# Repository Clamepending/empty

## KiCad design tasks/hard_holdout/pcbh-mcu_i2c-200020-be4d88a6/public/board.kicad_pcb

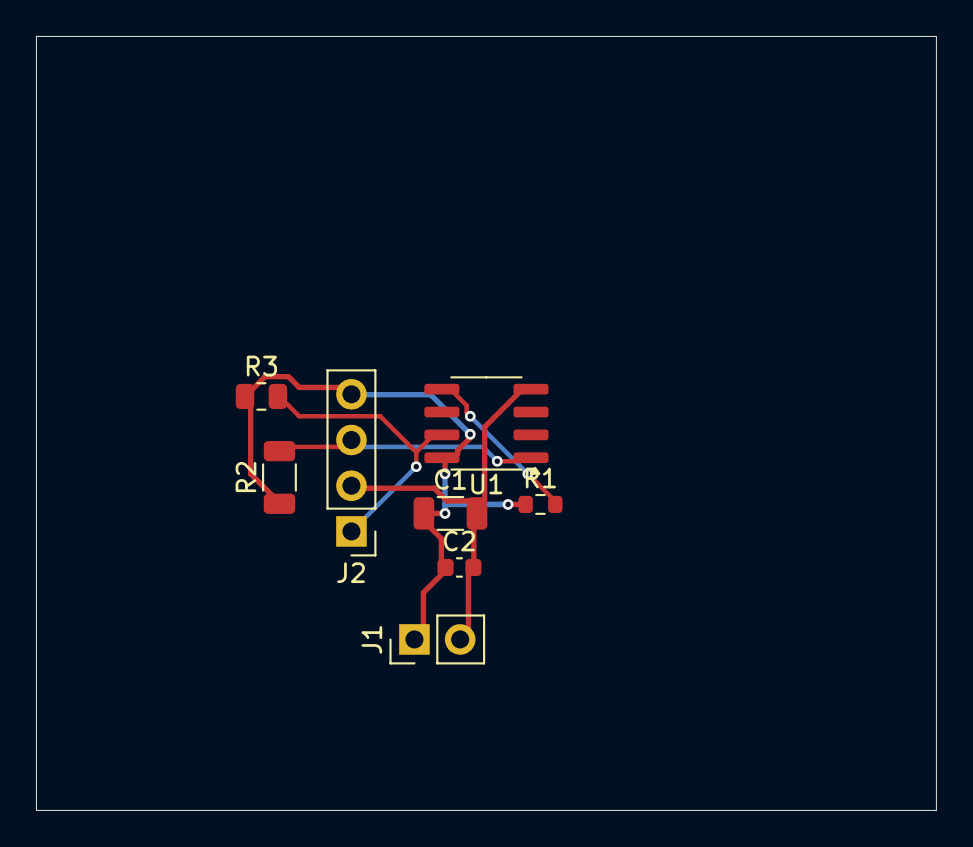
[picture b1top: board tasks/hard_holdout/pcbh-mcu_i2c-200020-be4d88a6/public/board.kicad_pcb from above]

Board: 2 copper layers, 50.0 x 43.0 mm, 8 parts (0 on the bottom side), 5 nets.

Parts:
C1: 100n; C_1206_3216Metric
C2: 1u; C_0603_1608Metric
J1: PinHeader_1x02_P2.54mm_Vertical
J2: PinHeader_1x04_P2.54mm_Vertical
R1: 43k; R_0603_1608Metric
R2: 3.6k; R_1206_3216Metric
R3: 39k; R_0805_2012Metric
U1: SOIC-8_3.9x4.9mm_P1.27mm

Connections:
+2V5: C1.1, C2.1, J1.1, J2.4, R1.1, R2.1, R3.1, U1.8
GND: C1.2, C2.2, J1.2, J2.2, U1.4
NRST: R1.2, U1.5
SCL: J2.1, R3.2, U1.7
SDA: J2.3, R2.2, U1.1

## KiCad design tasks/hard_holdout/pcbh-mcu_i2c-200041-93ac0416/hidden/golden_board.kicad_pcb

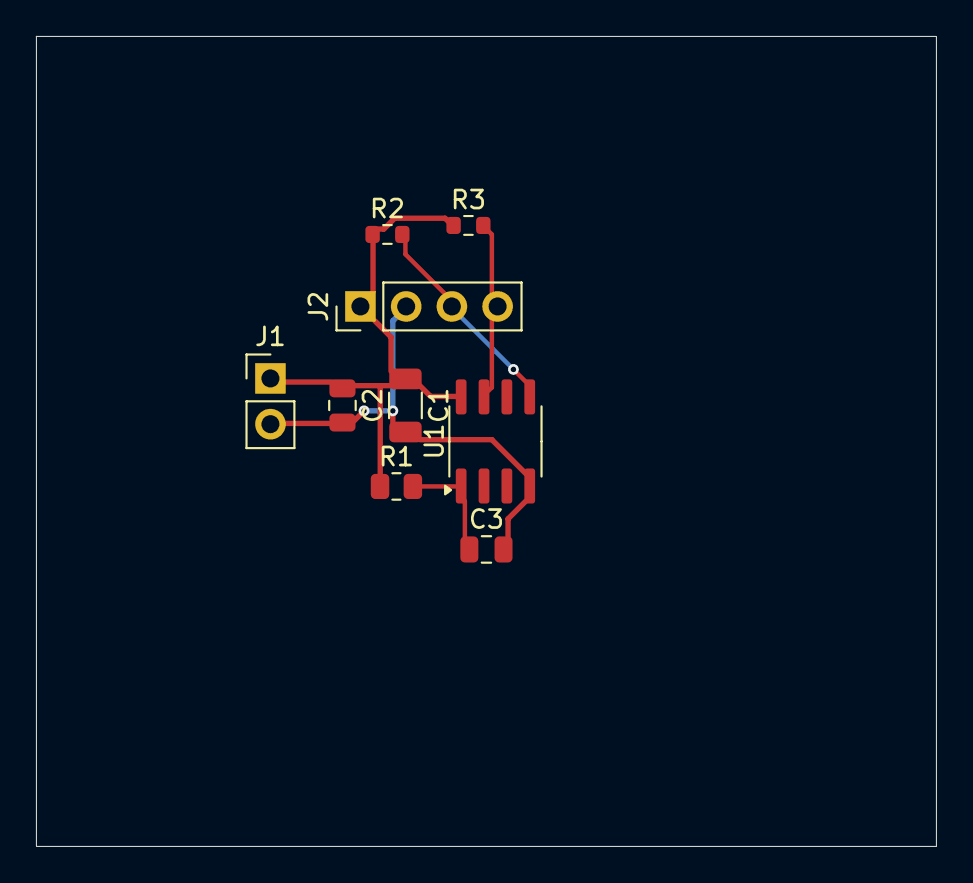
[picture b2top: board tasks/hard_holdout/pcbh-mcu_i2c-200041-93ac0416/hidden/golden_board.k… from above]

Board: 2 copper layers, 50.0 x 45.0 mm, 9 parts (0 on the bottom side), 5 nets.

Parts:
C1: 100n; C_1206_3216Metric
C2: 4.7u; C_0805_2012Metric
C3: 100n; C_0805_2012Metric
J1: PinHeader_1x02_P2.54mm_Vertical
J2: PinHeader_1x04_P2.54mm_Vertical
R1: 8.2k; R_0805_2012Metric
R2, R3: 6.8k; R_0603_1608Metric
U1: SOIC-8_3.9x4.9mm_P1.27mm

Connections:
+2V5: C1.1, C2.1, J1.1, J2.1, R1.1, R2.1, R3.1, U1.8
GND: C1.2, C2.2, C3.2, J1.2, J2.2, U1.4
NRST: C3.1, R1.2, U1.1
SCL: J2.4, R3.2, U1.7
SDA: J2.3, R2.2, U1.5

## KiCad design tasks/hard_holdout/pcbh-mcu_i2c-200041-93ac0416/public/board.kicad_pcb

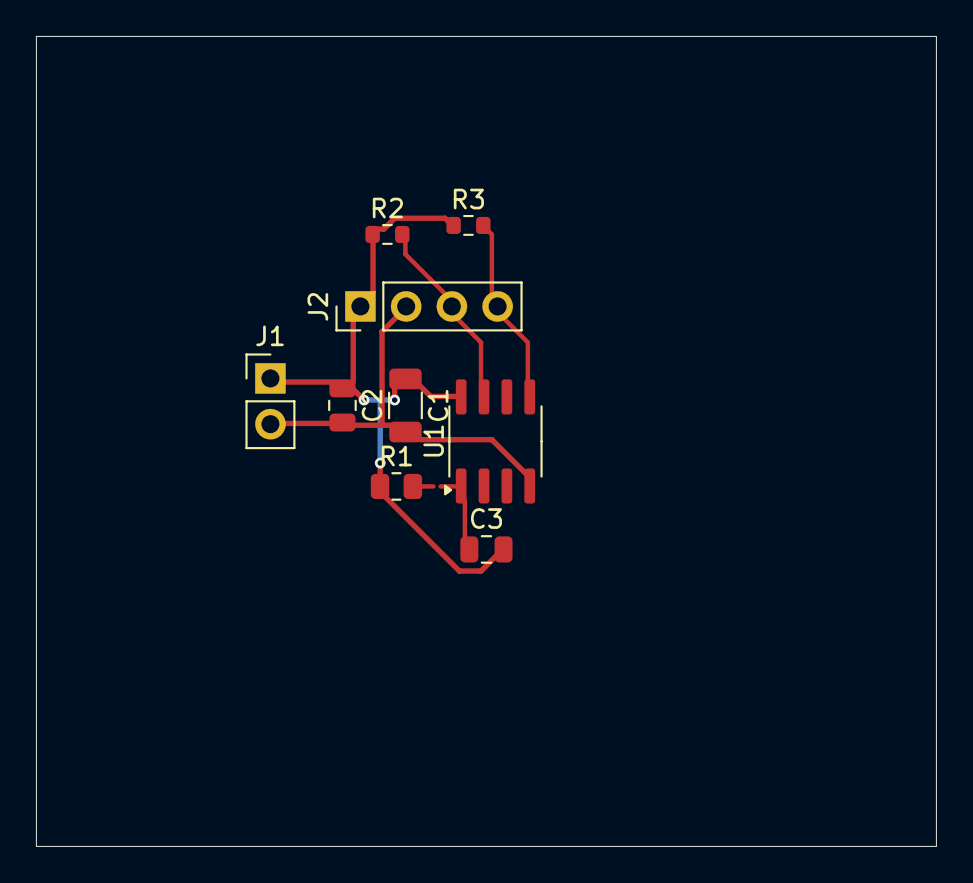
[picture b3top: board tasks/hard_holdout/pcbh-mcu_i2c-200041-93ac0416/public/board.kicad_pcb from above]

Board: 2 copper layers, 50.0 x 45.0 mm, 9 parts (0 on the bottom side), 5 nets.

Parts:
C1: 10n; C_1206_3216Metric
C2: 4.7u; C_0805_2012Metric
C3: 100n; C_0805_2012Metric
J1: PinHeader_1x02_P2.54mm_Vertical
J2: PinHeader_1x04_P2.54mm_Vertical
R1: 8.2k; R_0805_2012Metric
R2, R3: 6.8k; R_0603_1608Metric
U1: SOIC-8_3.9x4.9mm_P1.27mm

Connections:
+2V5: C1.1, C2.1, C3.2, J1.1, J2.1, R1.1, R2.1, R3.1, U1.8
GND: C1.2, C2.2, J1.2, J2.2, U1.4
NRST: C3.1, R1.2, U1.1
SCL: J2.4, R3.2, U1.5
SDA: J2.3, R2.2, U1.7

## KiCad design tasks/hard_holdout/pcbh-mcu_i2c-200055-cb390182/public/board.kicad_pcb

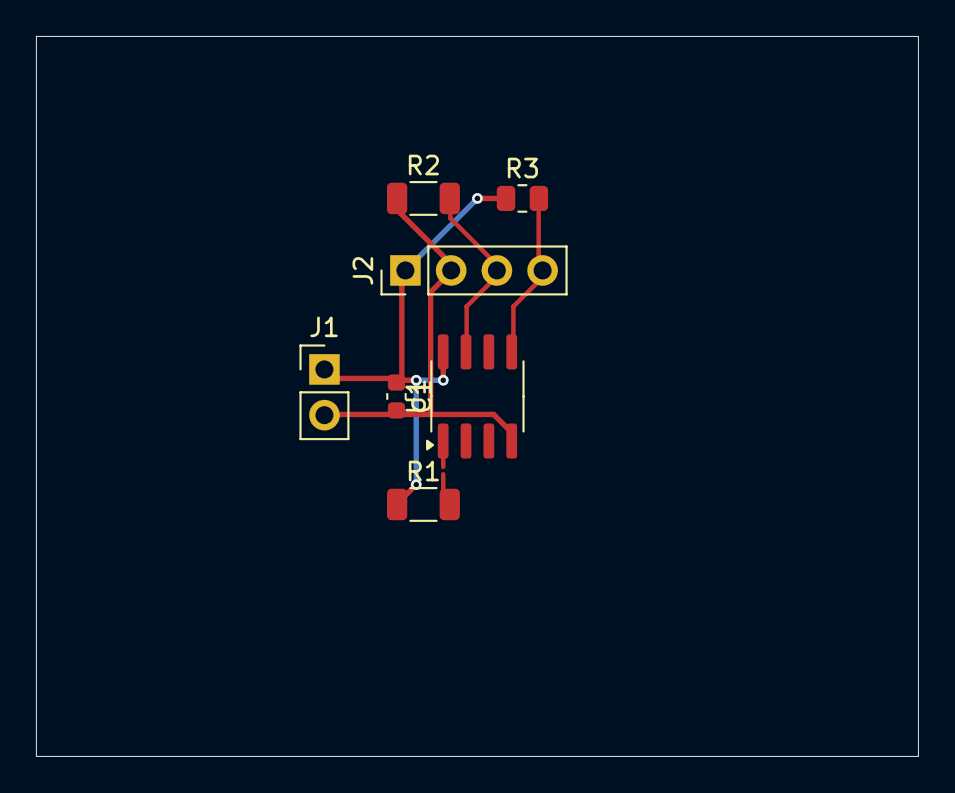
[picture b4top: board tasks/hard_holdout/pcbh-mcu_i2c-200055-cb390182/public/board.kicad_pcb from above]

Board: 2 copper layers, 49.0 x 40.0 mm, 7 parts (0 on the bottom side), 5 nets.

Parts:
C1: 100n; C_0603_1608Metric
J1: PinHeader_1x02_P2.54mm_Vertical
J2: PinHeader_1x04_P2.54mm_Vertical
R1: 27k; R_1206_3216Metric
R2: 1.1k; R_1206_3216Metric
R3: 1.1k; R_0805_2012Metric
U1: SOIC-8_3.9x4.9mm_P1.27mm

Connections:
+2V5: C1.1, J1.1, J2.1, R1.1, R3.1, U1.8
GND: C1.2, J1.2, J2.2, R2.1, U1.4
NRST: R1.2, U1.1
SCL: J2.4, R3.2, U1.5
SDA: J2.3, R2.2, U1.7

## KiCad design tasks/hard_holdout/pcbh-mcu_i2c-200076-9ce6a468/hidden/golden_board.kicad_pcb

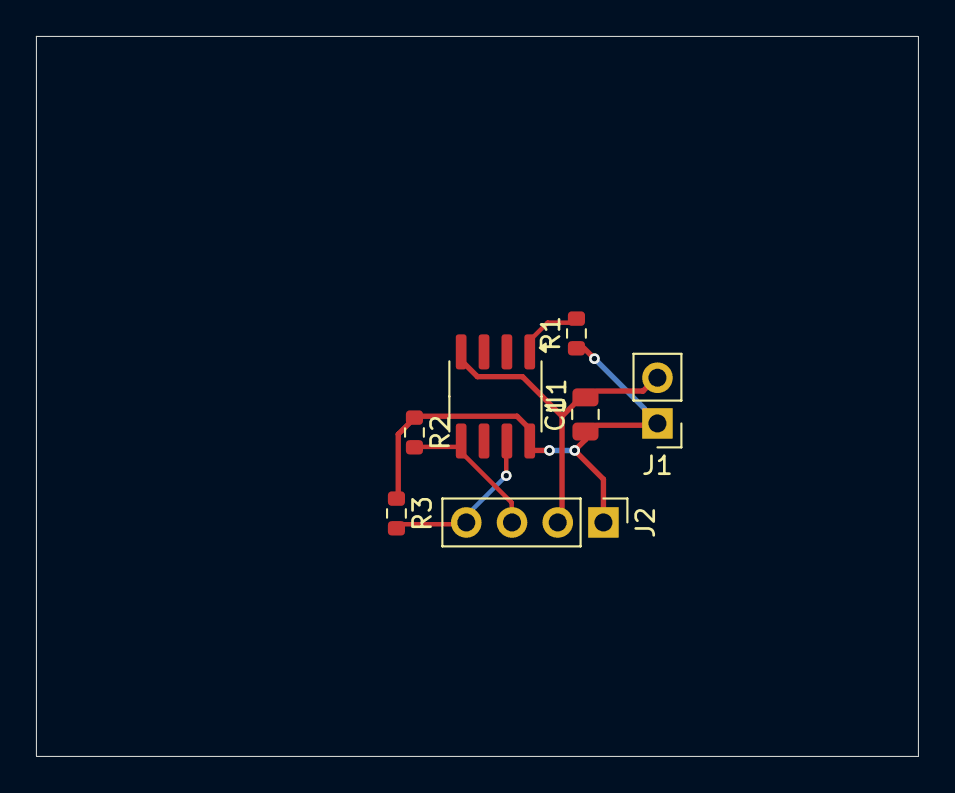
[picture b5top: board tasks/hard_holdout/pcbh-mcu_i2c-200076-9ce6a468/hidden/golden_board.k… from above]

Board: 2 copper layers, 49.0 x 40.0 mm, 7 parts (0 on the bottom side), 5 nets.

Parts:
C1: 100n; C_0805_2012Metric
J1: PinHeader_1x02_P2.54mm_Vertical
J2: PinHeader_1x04_P2.54mm_Vertical
R1: 6.8k; R_0603_1608Metric
R2, R3: 1.5k; R_0603_1608Metric
U1: SOIC-8_3.9x4.9mm_P1.27mm

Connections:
+3V3: C1.1, J1.1, J2.1, R1.1, R2.1, R3.1, U1.8
GND: C1.2, J1.2, J2.2, U1.4
NRST: R1.2, U1.1
SCL: J2.4, R3.2, U1.7
SDA: J2.3, R2.2, U1.5

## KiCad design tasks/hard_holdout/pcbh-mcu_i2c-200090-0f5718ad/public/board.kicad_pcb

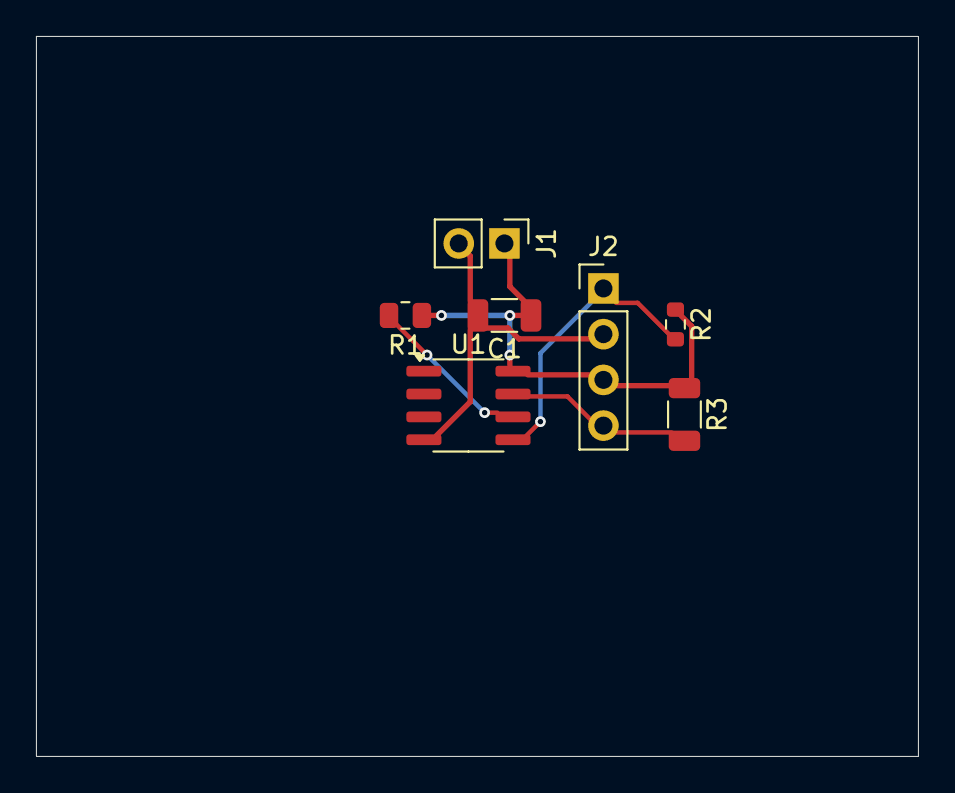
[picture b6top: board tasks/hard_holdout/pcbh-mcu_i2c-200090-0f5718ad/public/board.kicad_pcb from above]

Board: 2 copper layers, 49.0 x 40.0 mm, 7 parts (0 on the bottom side), 5 nets.

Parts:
C1: 100n; C_1206_3216Metric
J1: PinHeader_1x02_P2.54mm_Vertical
J2: PinHeader_1x04_P2.54mm_Vertical
R1: 30k; R_0805_2012Metric
R2: 4.7k; R_0603_1608Metric
R3: 4.7k; R_1206_3216Metric
U1: SOIC-8_3.9x4.9mm_P1.27mm

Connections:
+5V: C1.1, J1.1, J2.3, R1.1, R2.1, R3.1, U1.8
GND: C1.2, J1.2, J2.2, U1.4
NRST: R1.2, U1.6
SCL: J2.4, R3.2, U1.7
SDA: J2.1, R2.2, U1.5
